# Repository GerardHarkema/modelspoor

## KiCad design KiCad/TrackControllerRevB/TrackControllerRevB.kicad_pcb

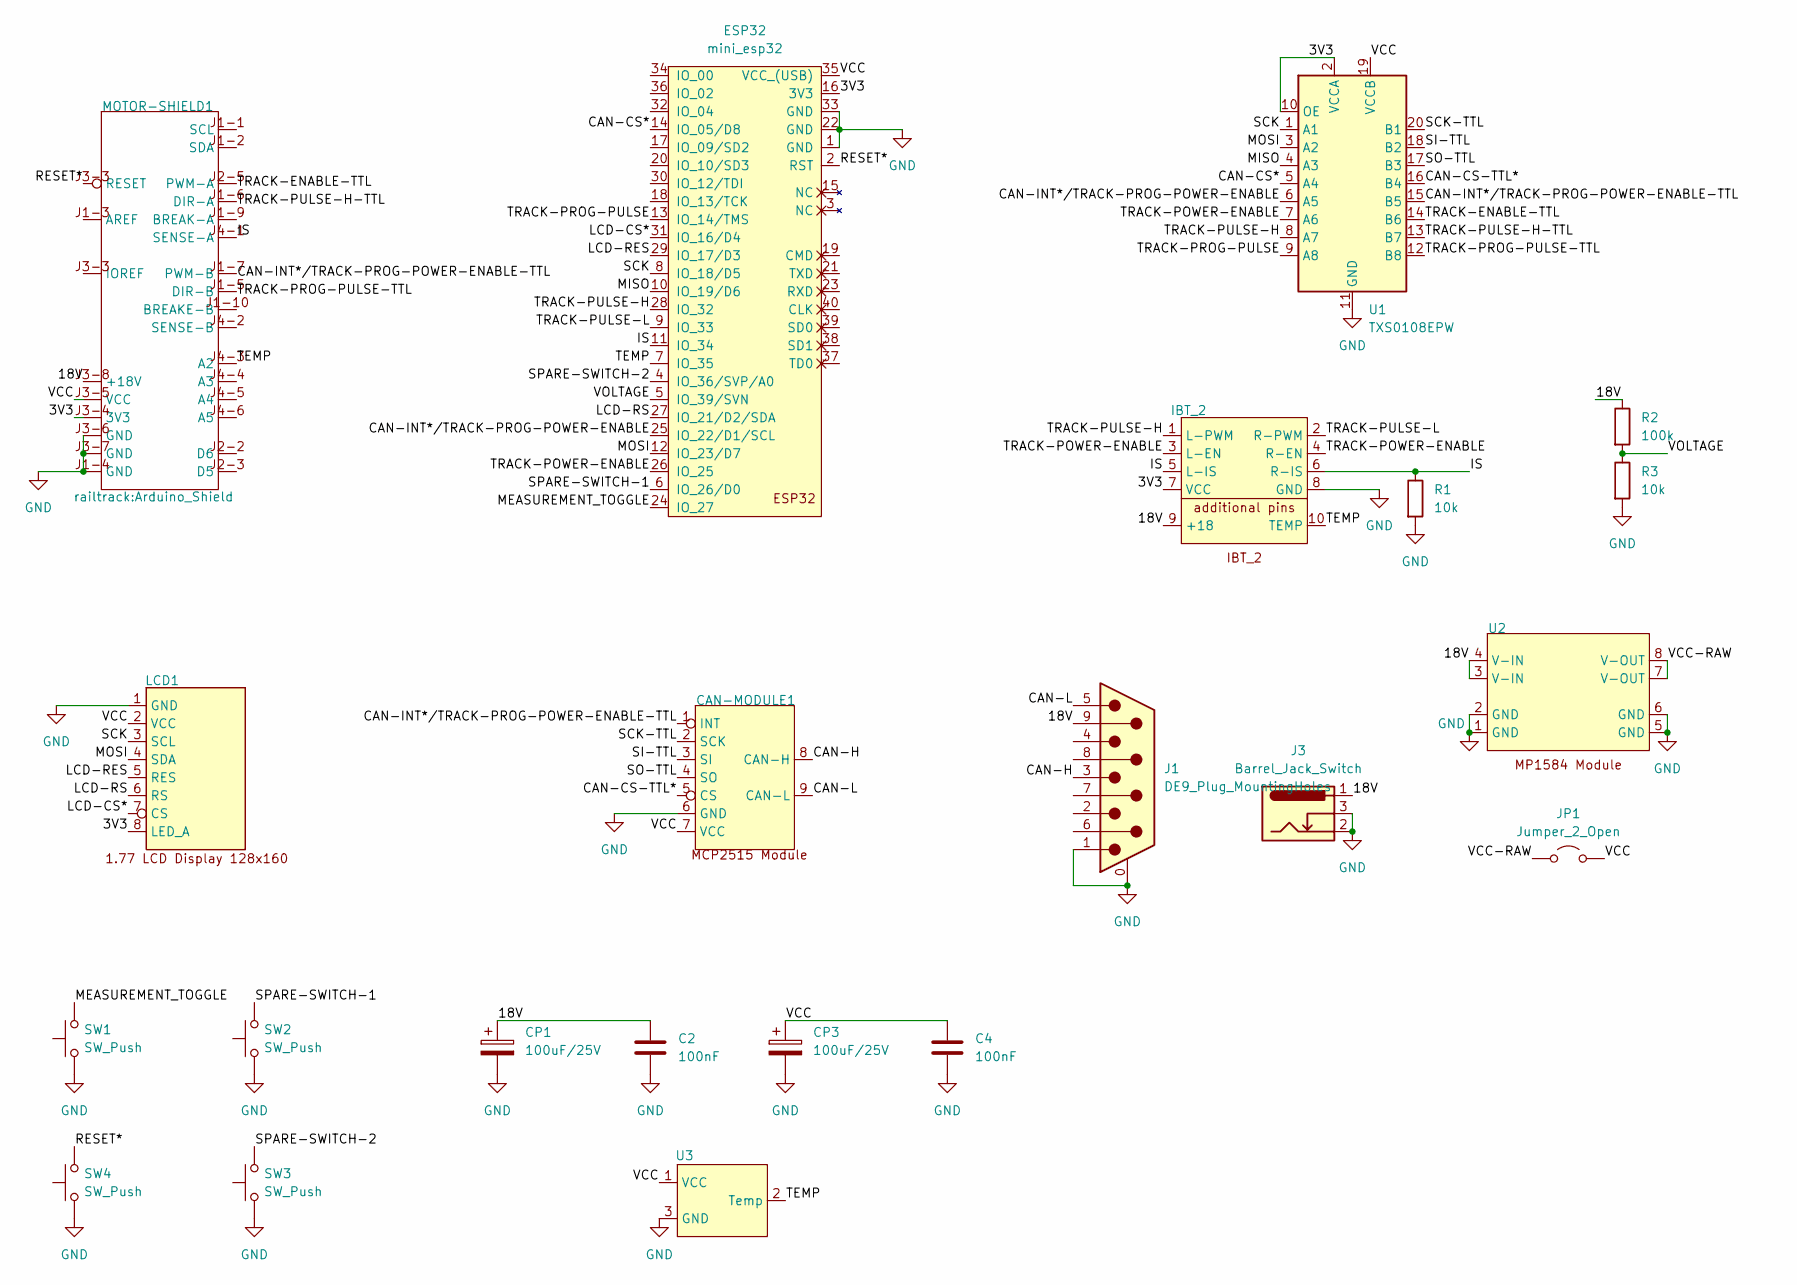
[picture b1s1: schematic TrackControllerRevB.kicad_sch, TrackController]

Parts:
C2, C4: 100nF; C_Disc_D5.1mm_W3.2mm_P5.00mm
CAN-MODULE1: MCP2515 Module
CP1, CP3: 100uF/25V; CP_Radial_D8.0mm_P5.00mm
ESP32: mini_esp32; ESP32_mini
IBT_2: IBT_2
J1: DE9_Plug_MountingHoles; DSUB-9_Male_Horizontal_P2.77x2.84mm_EdgePinOffset4.94mm_Hou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
J3: Barrel_Jack_Switch; BarrelJack_GCT_DCJ200-10-A_Horizontal
JP1: Jumper_2_Open; PinHeader_1x02_P2.54mm_Vertical
LCD1: 1.77 LCD Display 128x160
MOTOR-SHIELD1: Arduino_Shield
R1, R3: 10k; R_Axial_DIN0207_L6.3mm_D2.5mm_P7.62mm_Horizontal
R2: 100k; R_Axial_DIN0207_L6.3mm_D2.5mm_P7.62mm_Horizontal
SW1, SW2, SW3, SW4: SW_Push; SW_PUSH_6mm
U1: TXS0108EPW; Texas_TXS0108E_Level_Shifter_Module
U2: MP1484 Module
U3: TO-92

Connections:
/3V3: ESP32.16 (3V3), IBT_2.7 (VCC), LCD1.8 (LED_A), MOTOR-SHIELD1.J3-4 (3V3), U1.2 (VCCA), U1.10 (OE)
/18V: C2.1, CP1.1, IBT_2.9 (+18), J1.9, J3.1, MOTOR-SHIELD1.J3-8 (+18V), R2.1, U2.3 (V-IN), U2.4 (V-IN)
/CAN-CS*: ESP32.14 (IO_05/D8), U1.5 (A4)
/CAN-CS-TTL*: CAN-MODULE1.5 (CS), U1.16 (B4)
/CAN-H: CAN-MODULE1.8 (CAN-H), J1.3
/CAN-INT*/TRACK-PROG-POWER-ENABLE: ESP32.25 (IO_22/D1/SCL), U1.6 (A5)
/CAN-INT*/TRACK-PROG-POWER-ENABLE-TTL: CAN-MODULE1.1 (INT), MOTOR-SHIELD1.J1-7 (PWM-B), U1.15 (B5)
/CAN-L: CAN-MODULE1.9 (CAN-L), J1.5
/IS: ESP32.11 (IO_34), IBT_2.5 (L-IS), IBT_2.6 (R-IS), MOTOR-SHIELD1.J4-1 (SENSE-A), R1.1
/LCD-CS*: ESP32.31 (IO_16/D4), LCD1.7 (CS)
/LCD-RES: ESP32.29 (IO_17/D3), LCD1.5 (RES)
/LCD-RS: ESP32.27 (IO_21/D2/SDA), LCD1.6 (RS)
/MEASUREMENT_TOGGLE: ESP32.24 (IO_27), SW1.2
/MISO: ESP32.10 (IO_19/D6), U1.4 (A3)
/MOSI: ESP32.12 (IO_23/D7), LCD1.4 (SDA), U1.3 (A2)
/RESET*: ESP32.2 (RST), MOTOR-SHIELD1.J3-3 (RESET), SW4.2
/SCK: ESP32.8 (IO_18/D5), LCD1.3 (SCL), U1.1 (A1)
/SCK-TTL: CAN-MODULE1.2 (SCK), U1.20 (B1)
/SI-TTL: CAN-MODULE1.3 (SI), U1.18 (B2)
/SO-TTL: CAN-MODULE1.4 (SO), U1.17 (B3)
/SPARE-SWITCH-1: ESP32.6 (IO_26/D0), SW2.2
/SPARE-SWITCH-2: ESP32.4 (IO_36/SVP/A0), SW3.2
/TEMP: ESP32.7 (IO_35), IBT_2.10 (TEMP), MOTOR-SHIELD1.J4-3 (A2), U3.2 (Temp)
/TRACK-ENABLE-TTL: MOTOR-SHIELD1.J2-5 (PWM-A), U1.14 (B6)
/TRACK-POWER-ENABLE: ESP32.26 (IO_25), IBT_2.3 (L-EN), IBT_2.4 (R-EN), U1.7 (A6)
/TRACK-PROG-PULSE: ESP32.13 (IO_14/TMS), U1.9 (A8)
/TRACK-PROG-PULSE-TTL: MOTOR-SHIELD1.J1-5 (DIR-B), U1.12 (B8)
/TRACK-PULSE-H: ESP32.28 (IO_32), IBT_2.1 (L-PWM), U1.8 (A7)
/TRACK-PULSE-H-TTL: MOTOR-SHIELD1.J1-6 (DIR-A), U1.13 (B7)
/TRACK-PULSE-L: ESP32.9 (IO_33), IBT_2.2 (R-PWM)
/VCC: C4.1, CAN-MODULE1.7 (VCC), CP3.1, ESP32.35 (VCC_(USB)), JP1.2 (B), LCD1.2 (VCC), MOTOR-SHIELD1.J3-5 (VCC), U1.19 (VCCB), U3.1 (VCC)
/VCC-RAW: JP1.1 (A), U2.7 (V-OUT), U2.8 (V-OUT)
/VOLTAGE: ESP32.5 (IO_39/SVN), R2.2, R3.1
GND: C2.2, C4.2, CAN-MODULE1.6 (GND), CP1.2, CP3.2, ESP32.1 (GND), ESP32.22 (GND), ESP32.33 (GND), IBT_2.8 (GND), J1.0 (PAD), J1.1, J3.2, J3.3, LCD1.1 (GND), MOTOR-SHIELD1.J1-4 (GND), MOTOR-SHIELD1.J3-6 (GND), MOTOR-SHIELD1.J3-7 (GND), R1.2, R3.2, SW1.1, SW2.1, SW3.1, SW4.1, U1.11 (GND), U2.1 (GND), U2.2 (GND), U2.5 (GND), U2.6 (GND), U3.3 (GND)

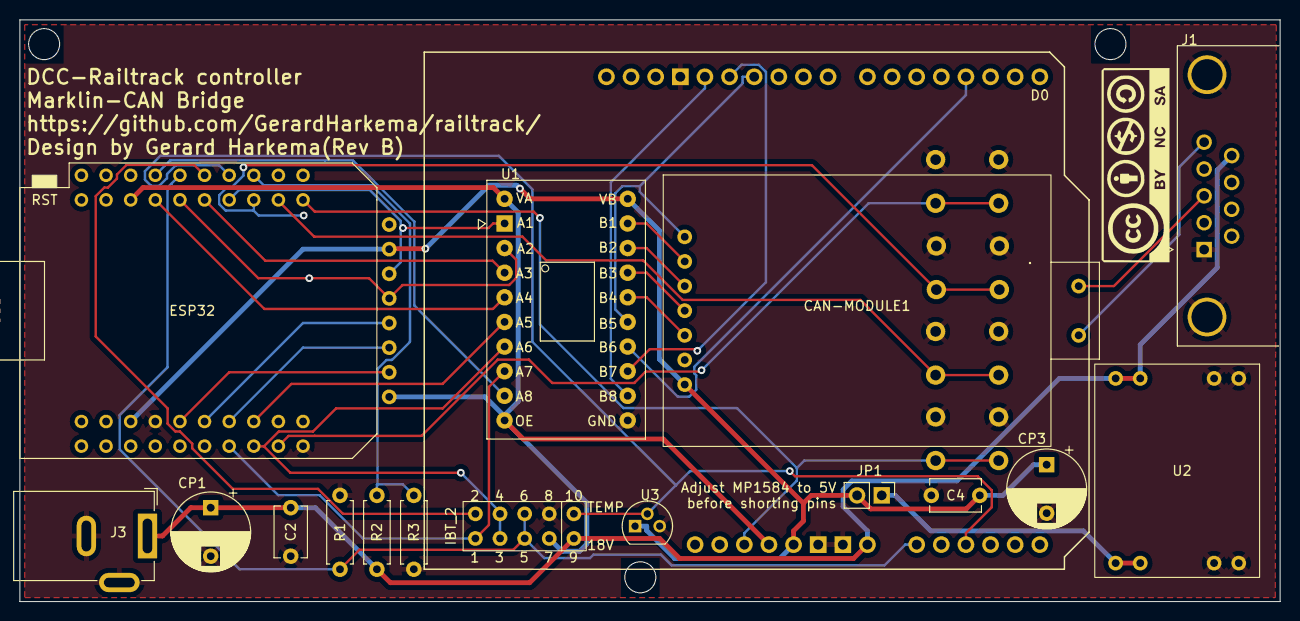
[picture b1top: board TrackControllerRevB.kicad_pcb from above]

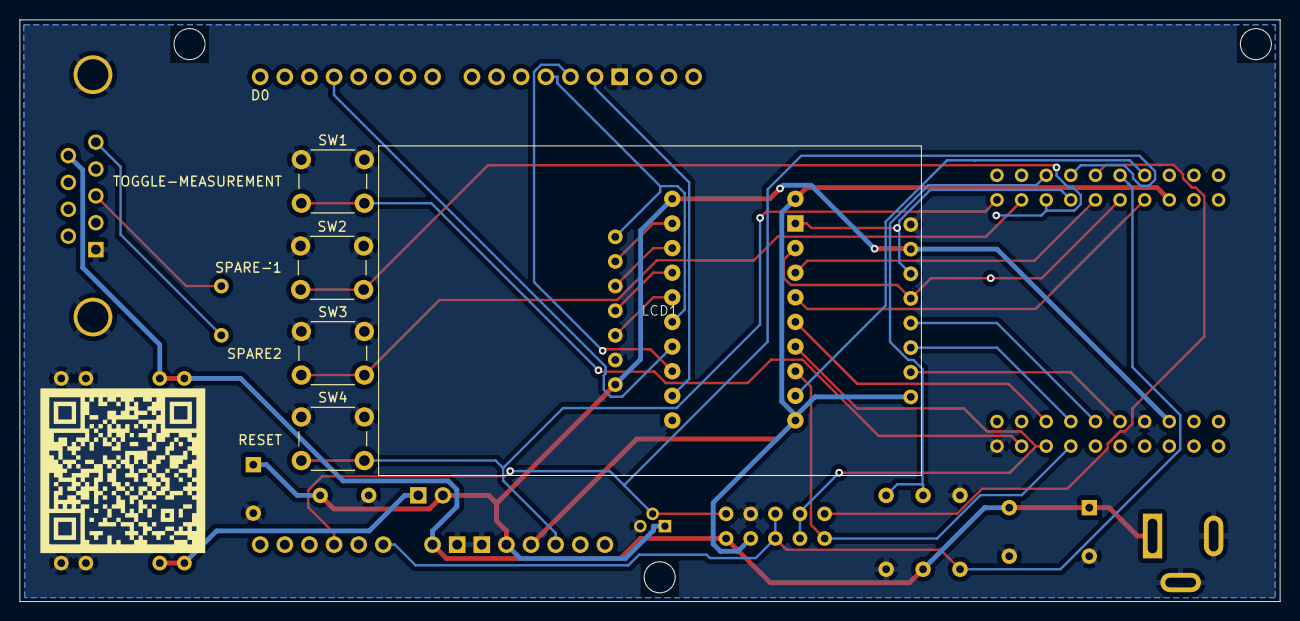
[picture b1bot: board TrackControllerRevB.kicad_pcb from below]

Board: 2 copper layers, 130.0 x 60.0 mm, 23 parts (5 on the bottom side), 34 nets.

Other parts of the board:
G1: LOGO

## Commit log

2023-12-10 20231210
2023-12-13 20231213
2023-12-17 20231217
2023-12-24 20231224
2023-12-25 20231225
2023-12-26 20231226
2024-01-01 20240101
2024-01-01 20240101-2
2024-01-02 20240102
2024-01-04 20240104
2024-01-05 20240105
2024-01-05 20240105-2
2024-01-06 20240106
2024-01-10 20240110
2024-01-13 20230113
2024-01-15 20230115
2024-01-16 20240116
2024-01-17 20240117
2024-01-21 20240121
2024-01-22 20240122
2024-01-23 20230123
2024-01-25 20240125
2024-01-28 20240128
2024-01-29 20240129
2024-01-30 20240130
2024-01-31 20240131
2024-02-01 20240201
2024-02-02 20240202-1
2024-02-02 20240202-2
2024-02-02 20240202-3
2024-02-02 20240202-4
2024-02-03 20240203
2024-02-04 20240204
2024-02-04 20240204-1
2024-02-07 20240207
2024-02-08 20240208
2024-02-09 20240209
2024-02-10 20240210
2024-02-10 20240210-2
2024-02-11 20240211
2024-02-12 20240212
2024-02-13 20240213
2024-02-14 20240214
2024-02-15 20240215
2024-02-16 20240216
2024-02-18 20240218
2024-02-22 20240222
2024-02-22 Split projects in railtrack & modelspoor
2024-03-27 20240427
2024-04-29 Added KiCad design
2024-05-01 20240501
2024-05-07 Added Rev B PCB support
2024-05-08 20240508
2024-05-14 2040514
